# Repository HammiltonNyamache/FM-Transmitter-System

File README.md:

# FM Transmitter System (KiCad Project)

This repository contains the schematic and PCB design for an FM transmitter system created using KiCad.

---

## Schematic

---

## PCB 3D View

### Front View

### Back View

---

## Project Files
- KiCad schematic
- PCB layout
- Gerber manufacturing files

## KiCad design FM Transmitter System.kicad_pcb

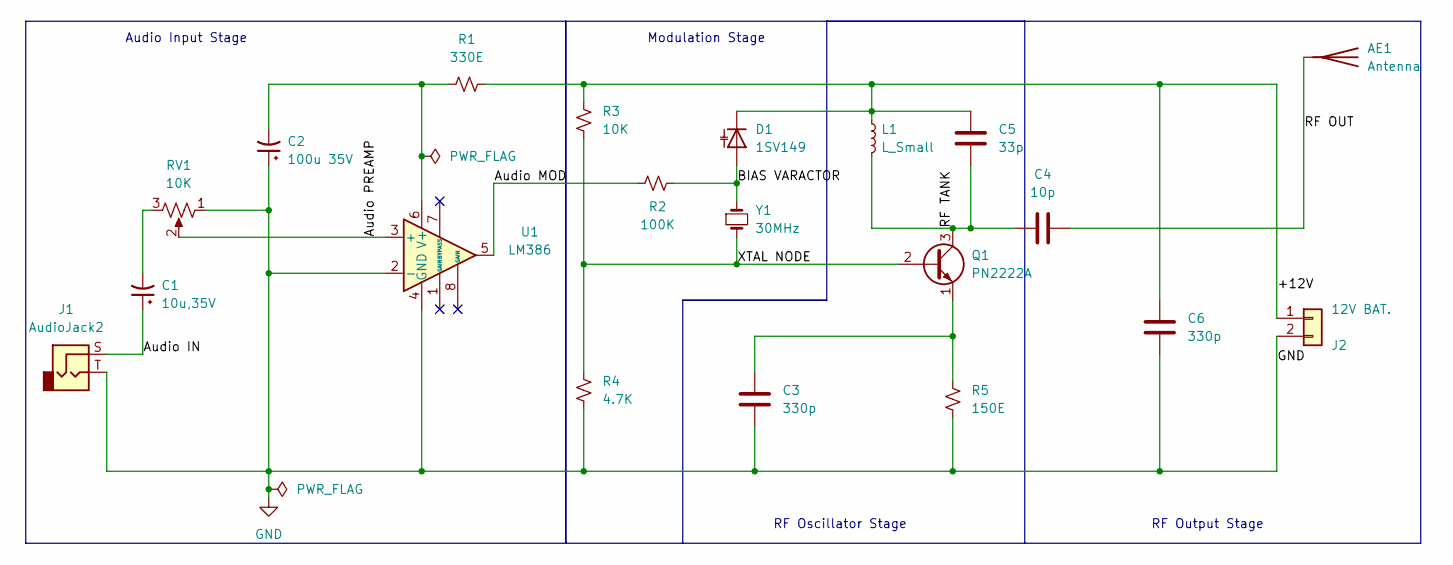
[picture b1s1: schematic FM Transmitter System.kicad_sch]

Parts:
AE1: Antenna; SMA_Amphenol_132134_Vertical
C1: 10u,35V; CP_Radial_D8.0mm_P2.50mm
C2: 100u 35V; CP_Radial_D8.0mm_P2.50mm
C3, C6: 330p; CP_Radial_D4.0mm_P2.00mm
C4: 10p; CP_Radial_D4.0mm_P2.00mm
C5: 33p; CP_Radial_D4.0mm_P2.00mm
D1: 1SV149; D_T-1_P5.08mm_Horizontal
J1: AudioJack2; Jack_3.5mm_CUI_SJ1-3533NG_Horizontal_CircularHoles
J2: 12V BAT.; PinHeader_1x02_P2.54mm_Vertical
L1: L_Small; L_Axial_L5.3mm_D2.2mm_P2.54mm_Vertical_Vishay_IM-1
Q1: PN2222A; TO-92_Inline
R1: 330E; R_Axial_DIN0204_L3.6mm_D1.6mm_P5.08mm_Horizontal
R2: 100K; R_Axial_DIN0204_L3.6mm_D1.6mm_P5.08mm_Horizontal
R3: 10K; R_Axial_DIN0204_L3.6mm_D1.6mm_P5.08mm_Horizontal
R4: 4.7K; R_Axial_DIN0204_L3.6mm_D1.6mm_P5.08mm_Horizontal
R5: 150E; R_Axial_DIN0204_L3.6mm_D1.6mm_P5.08mm_Horizontal
RV1: 10K; Potentiometer_Bourns_3296Y_Vertical
U1: LM386; DIP-8_W7.62mm
Y1: 30MHz; Crystal_HC49-U_Vertical

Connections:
/+12V: C5.1, C6.1, D1.1 (K), J2.1, L1.1, R1.2, R3.1
/Audio IN: C1.1, J1.S
/Audio MOD: R2.1, U1.5
/Audio PREAMP: RV1.2, U1.3 (+)
/BIAS VARACTOR: D1.2 (A), R2.2, Y1.1
/RF OUT: AE1.1 (A), C4.2
/RF TANK: C4.1, C5.2, L1.2, Q1.3 (C)
/XTAL NODE: Q1.2 (B), R3.2, R4.1, Y1.2
GND: C2.1, C3.2, C6.2, J1.T, J2.2, R4.2, R5.2, RV1.1, U1.2 (-), U1.4 (GND)
unnamed: C1.2, RV1.3
unnamed: C3.1, Q1.1 (E), R5.1
unnamed: C2.2, R1.1, U1.6 (V+)

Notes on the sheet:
Audio Input Stage
RF Oscillator Stage
Modulation Stage
RF Output Stage

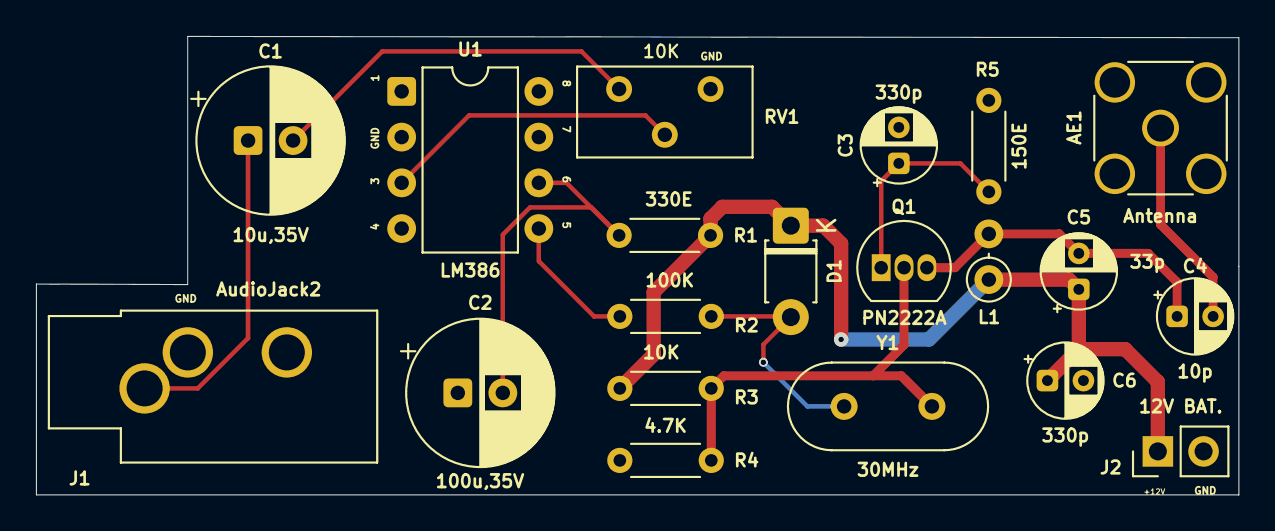
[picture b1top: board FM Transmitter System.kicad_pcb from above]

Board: 2 copper layers, 66.8 x 25.5 mm, 20 parts (0 on the bottom side), 12 nets.

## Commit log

2026-03-06 Initial commit: FM Transmitter System project
2026-03-06 Update README with project details and images
    Added detailed project information including schematic, 3D PCB view, project files, and software used.
2026-03-06 Update schematic image in README
2026-03-06 Revise README for clarity and image references
    Updated descriptions and image paths in README.md.
2026-03-06 Fix image file names in README.md
    Updated image file names in README for consistency.
2026-03-06 Fix image links in README.md
    Updated image file names in README for consistency.
2026-03-06 Rename FM Transmitter System F.SILK.jpg to pcbfront
2026-03-06 Rename FM Transmitter System B.SILK.jpg to pcbback
2026-03-06 Update PCB images in README
2026-03-25 Created using Colab
